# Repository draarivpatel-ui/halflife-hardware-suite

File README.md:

# halflife-hardware-suite

Five hardware design studies built for [Hack Club Half Life](https://halflife.hackclub.com/) and the parametric CAD practice of [Hack Club Atlantis](https://atlantis.hackclub.com/), plus a zero-dependency browser workbench that inspects all five. Everything is checked in as source, fabrication output, firmware, and repeatable tests. No build step, no package manager, no external assets.

Live workbench: <https://aariv.me/halflife-hardware-suite/>

> **PCB fabrication status: not fabrication-ready.** A static audit on 2026-11-25 found incomplete copper connectivity in the week 1, 3, and 4 PCB sources. It also confirmed that weeks 3 and 4 currently emit no board-derived copper tracks in their copper Gerbers because the generator falls back to synthetic pad grids when no exact board capture is passed. Do not upload any PCB Gerber zip until the boards are rerouted, the copper plots are regenerated from real board geometry, and both are independently revalidated.
Repository: <https://github.com/draarivpatel-ui/halflife-hardware-suite>

## Why this exists

Half Life runs five weekly design tracks before five weeks of building: **PCBs**, **CAD**, **music**, **displays**, and **breadboard logic**. Each track qualifies for up to `$100.00` in parts funding, and finishing the program earns a 3D printer and a Half Life sticker sheet. This suite treats each week as a real design exercise with a real BOM, real fabrication files, and a real verification harness rather than a slide deck.

| Week | Track | Project | Board / part count | BOM total |
| --- | --- | --- | --- | --- |
| 1 | PCB | `BenchRail-INA` USB-C dual-rail precision current and voltage monitor | 62 x 42 mm, 2 layer | `$6.90` |
| 2 | CAD | `HelicalDesk` parametric 3-stage snap-fit stand and rotary detent pod | 3 STL + 1 OBJ | print only |
| 3 | Music | `PocketChime-R2R` 8-bit ladder chiptune synthesizer | 78 x 56 mm, 2 layer | `$12.19` |
| 4 | Displays | `GlyphMatrix-128` dual SSD1306 OLED + 74HC595 8x8 LED badge | 88 x 54 mm, 2 layer | `$18.56` |
| 5 | Breadboard logic | `DiscreteALU-74HC` 4-bit CMOS ALU and step counter | 9 DIP ICs | `$12.60` |

All four priced BOMs sit far below the `$100.00` per-project allowance and below the tighter internal caps of `$18.00`, `$22.00`, `$24.00`, and `$16.00`. The combined priced total is `$50.25`, leaving room for shipping, spare passives, and a second prototype round.

## Quick start

```bash
git clone https://github.com/draarivpatel-ui/halflife-hardware-suite.git
cd halflife-hardware-suite
node --test
```

Open `index.html` in any modern browser. It uses plain HTML, CSS, and JavaScript, so it also works from a local file; a static server gives the workbench live access to the checked-in KiCad, STL, and netlist sources. No npm install, no bundler, no CDN.

```bash
python3 -m http.server 8000
# then visit http://localhost:8000/
```

To regenerate every deterministic artifact from one place:

```bash
node tools/generate_suite_artifacts.js
```

The generator uses a seeded PRNG, so re-running it leaves the KiCad boards, Gerbers, drill files, BOMs, STL, OBJ, netlist, and font tables unchanged. The OpenSCAD source remains the authoritative printable geometry for Week 2.

## The five designs

### Week 1: `week1-pcb/` BenchRail-INA

A USB-C powered dual-rail telemetry board. Two `INA219AIDCNR` monitors read independent 0.1 ohm 1% 1206 shunts, one per rail, at I2C addresses 0x40 and 0x41. An `AMS1117-3.3` LDO supplies the logic, a `USB4105-GF-A` receptacle brings in 5 V with 5K1 CC pulldowns, and 0603 decoupling caps sit at every IC. Four M2.5 non-plated mounting holes and a full ground pour complete the layout.

Files: `benchrail_ina.kicad_sch`, `benchrail_ina.kicad_pcb`, `benchrail_ina.kicad_pro`, `gerbers/` (9 RS-274X plots plus Excellon `.drl`), `bom.csv`.

The `.kicad_pro` declares three net classes: Default (0.20 mm clearance / 0.25 mm track), Power (0.25 mm / 0.60 mm), and Signal (0.15 mm / 0.20 mm). Patterns assign VBUS and 3V3 to Power, SDA and SCL to Signal.

**Power-up check:** current-limited 5 V supply, all DIP switches off, idle draw below 30 mA; read the bus voltage register and confirm the calibration word 0x2800 for a 0.1 ohm shunt at a 40 uA LSB.

### Week 2: `week2-cad/` HelicalDesk

`helical_desk.scad` is a fully parameterized OpenSCAD model with Customizer groups for chassis, cradle, dial, snap fit, and assembly. The three printable stages are a base chassis with a raised rim and M2.5 rotary boss, a tilt cradle with side cheeks, rear lip and hinge bore, and a 12-tooth detent dial. No supports are needed; PLA at 0.2 mm layers, 3 perimeters, 15% infill.

`tools/generate_suite_artifacts.js` mirrors the same parameter set and writes `base_chassis.stl`, `tilt_cradle.stl`, `detent_dial.stl`, and `assembled_preview.obj`. `week2-cad/geometry_stats.json` records half-edge pairing, connected components, and signed volume for each part. Every exported STL passes the strict check that each directed edge has exactly one exact opposite, all component volumes are positive, and all stored facet normals agree with their triangle windings.

### Week 3: `week3-music/` PocketChime-R2R

An 8-bit voltage-mode R-2R ladder built from eight 10K horizontal arms and eight 20K vertical legs (seven legs plus a 20K termination), all 0603 1%. An `RP2040-Zero` drives the eight GPIO bits as one bus write; a `MCP6002-I/SN` rail-to-rail dual op amp buffers the ladder into a 3.5 mm TRS jack. Twelve tactile switches form a 3x4 chromatic key matrix.

`firmware/pocketchime.ino` implements four phase-accumulator DDS voices (pulse, triangle, saw, square) and a four-stage ADSR running in a 22050 Hz repeating-timer ISR. The phase increment is `f * 2^32 / sample_rate`; the bus write is a masked GPIO operation.

The workbench solves the ladder by Gaussian elimination on the eight-node Kirchhoff system, giving a strictly monotonic 256-code transfer curve with a uniform 12.891 mV LSB at a 3.3 V reference.

### Week 4: `week4-display/` GlyphMatrix-128

Two 128x64 SSD1306 OLED modules on hardware I2C at 0x3C and 0x3D, plus an 8x8 LED matrix driven by a `74HC595` shift register. `firmware/glyphmatrix.ino` contains a complete SSD1306 init sequence, a 1 KiB page-buffer renderer, a 5x7 bitmap font, and a timer-multiplexed row scan with output blanking during the shift to prevent ghosting.

`font5x7_data.h` carries all 96 printable ASCII glyphs; `font5x7.js` and the root `suite_font.js` carry the full 256-glyph table for the browser simulator. No display library is used.

### Week 5: `week5-logic/` DiscreteALU-74HC

Eight 74HCxx DIP ICs on two 830-point breadboards. A `74HC283` full adder, `74HC86` XOR B-inversion stage, `74HC08` AND, `74HC32` OR, `74HC153` dual 4:1 output mux, `74HC161` step counter, `74HC14` Schmitt debounce, and `74HC02` NOR zero detector. Subtraction uses the two's complement trick: `SUB` drives all four XOR inputs and the adder CIN, so `A + (B XOR SUB) + SUB` equals `A - B`.

`netlist.json` records every physical DIP pin. The 74HC283 pin map was checked against the NXP datasheet Fig 5 (pin configuration), where pin 1 is S2, pin 7 is CIN, pin 9 is COUT, and pin 16 is VCC. `BREADBOARD_GUIDE.md` gives the gate maps, opcode table, flag equations, placement, and a seven-step power-up check. `alu.js` is a gate-level evaluator shared by the Node tests and the browser prover.

## Browser workbench

`index.html` is a six-tab engineering studio:

1. **PCB**: an SVG layer inspector that parses the checked-in `.kicad_pcb` for copper segments, pads, mounting holes, silkscreen text, and Edge.Cuts. Nine independently toggleable layers plus an INA219 register and power model.
2. **CAD**: a Canvas turntable that parses the real ASCII STL, flat-shades it with a depth sort and fixed light vector, supports shaded and wireframe modes, and reports half-edge pairing, signed volume, connected components, and normal agreement.
3. **Music**: the 256-code R-2R staircase alongside an ADSR / four-voice DDS oscilloscope. **No Web Audio object is created on load, on tab switch, or at any point without an explicit user click.** A muted-by-default checkbox creates a silent context; a separate Play control is required before any oscillator starts.
4. **Displays**: two 128x64 page buffers drawn pixel by pixel with a 5x7 font, plus a live 74HC595 8x8 row scan showing the shift register contents.
5. **Logic**: clickable operand bits, five opcodes, gate-level signal flow, flag LEDs, a pin-map browser for all nine ICs, a 74HC161 step counter, and an exhaustive 512 plus 1280 vector verifier.
6. **Lab**: a deterministic Suite Audit & Physics Lab driven by `suite-lab.js`, a pure UMD module with no DOM, network, or timers. It hosts a five-week cross-track comparator (BOM vs cap with headroom and a verified physics metric per week, clickable rows jump into each tab), an R-2R tolerance and INL/DNL sensitivity chart re-solving the real eight-node Kirchhoff system under 46 deterministic worst-case resistor patterns, an INA219 shunt power and ADC full-scale sweep, a clickable BOM-vs-cap budget frontier, and an audited proof brief whose on-page fingerprint, JSON, CSV (formula-injection escaped), and Markdown exports all stamp one cached canonical SHA-256 digest. Lab state round-trips through a fail-closed `#hlab=` URL hash, and an in-page runner executes a 25-check deterministic self-test battery (28 checks once the STL files load) against the live models.

`style.css` is a self-contained dark instrument-panel theme with responsive layouts and reduced-motion support. `.nojekyll` keeps GitHub Pages from ignoring the underscore-prefixed or data files.

## Verification

`node --test` runs 556 tests with thousands of individual assertions:

* KiCad 8 `(version 20240108)` PCB and `(version 20231120)` schematic headers, balanced S-expression parentheses, all nine required layers, net classes, routed copper, pads, courtyards, and four M2.5 holes per board.
* RS-274X `G04`, `%FSLAX46Y46*%`, `%MOMM*%`, aperture definitions, and a terminating `M02*` on all 27 Gerber plots; Excellon `M48`, `FMAT,2`, tool table, `G90`, `G05`, coordinate records, and `M30` on all three drill files.
* BOM CSV structure, real LCSC / DigiKey / JLCPCB part numbers, extended-price arithmetic, and the four price caps.
* STL half-edge manifoldness (every directed edge has its exact opposite), positive signed volume per connected component, and facet normal agreement with triangle winding; OBJ validity for the assembly.
* Exact 256-code R-2R monotonicity with uniform LSB steps, bounded DDS waveforms, and all four ADSR stages.
* SSD1306 1024-byte page-buffer set/get and text rendering, the 256-glyph 5x7 table, and the 74HC595 16-bit scan register model.
* All 512 ADD/SUB operand vectors with exact carry, zero, and overflow, plus all 1280 five-opcode vectors cross-checked between the browser model and `alu.js`.
* Byte-level scan of every file for zero em dashes, zero en dashes, zero AI self-references, backtick-wrapped dollar amounts in Markdown, and no personal contact details.
* The autoplay guard: exactly one `AudioContext` construction site, bound only to a change handler, with gain zero until the separate Play click.
* Lab (`suite-lab.test.js`, discovered beside `test.js`): FIPS 180-4 SHA-256 known-answer vectors plus a 0-to-160-byte boundary sweep against Node `crypto`, canonicalizer key-order, cycle, and depth-bound tests, hostile `#hlab=` codec rejection (`__proto__`, bad roots, bad base64url, clamp violations), R-2R generalized-solver parity with the suite solver across all 256 codes, tolerance-sweep invariants, INA219 sweep bounds, comparator BOM-vs-cap and metric verdicts cross-checked against the real CSVs, formula-injection CSV escaping, single-digest parity across all four export surfaces, one-unit tamper detection, a 160-vector ALU spot grid, the 25-check deterministic self-test battery, and DOM wiring assertions for the sixth tab.

## Repository layout

```
index.html  style.css  suite.js  suite-lab.js  app.js  suite_font.js
test.js  suite-lab.test.js  .nojekyll  README.md  JOURNAL.md  LICENSE
tools/
  generate_suite_artifacts.js   deterministic artifact generator
  font_data.txt                 256 glyph x 5 byte source table
week1-pcb/    kicad_sch  kicad_pcb  kicad_pro  gerbers/  benchrail_ina-gerbers.zip  bom.csv
week2-cad/    helical_desk.scad  3x stl  assembled_preview.obj  geometry_stats.json
week3-music/  kicad_pcb  kicad_pro  gerbers/  pocketchime-gerbers.zip  bom.csv  firmware/pocketchime.ino
week4-display/ kicad_pcb  kicad_pro  gerbers/  glyphmatrix-gerbers.zip  bom.csv  firmware/  font5x7.js
week5-logic/  netlist.json  BREADBOARD_GUIDE.md  alu.js  bom.csv
```

## Fabrication notes

* All PCBs are 2 layer, 1.6 mm FR4, 0.035 mm copper, ENIG finish, green mask, with a 1.51 mm FR4 dielectric core.
* Gerbers use 4.6 format, millimetres, Gerber X2 `%TF.FileFunction` and `%TF.FilePolarity` attributes, and 4.4 metric drill coordinates.
&
* BOM prices are single-unit catalog prices captured for this build. They exclude shipping and customs, which Half Life does not cover.
* Week 2 prints without supports. Allow a 0.2 mm bore clearance on the M2.5 hinge.
* Week 5 uses a current-limited 5 V bench supply and expects under 20 mA idle draw. Tie every unused CMOS input to a defined rail.

## License

MIT. See `LICENSE`.

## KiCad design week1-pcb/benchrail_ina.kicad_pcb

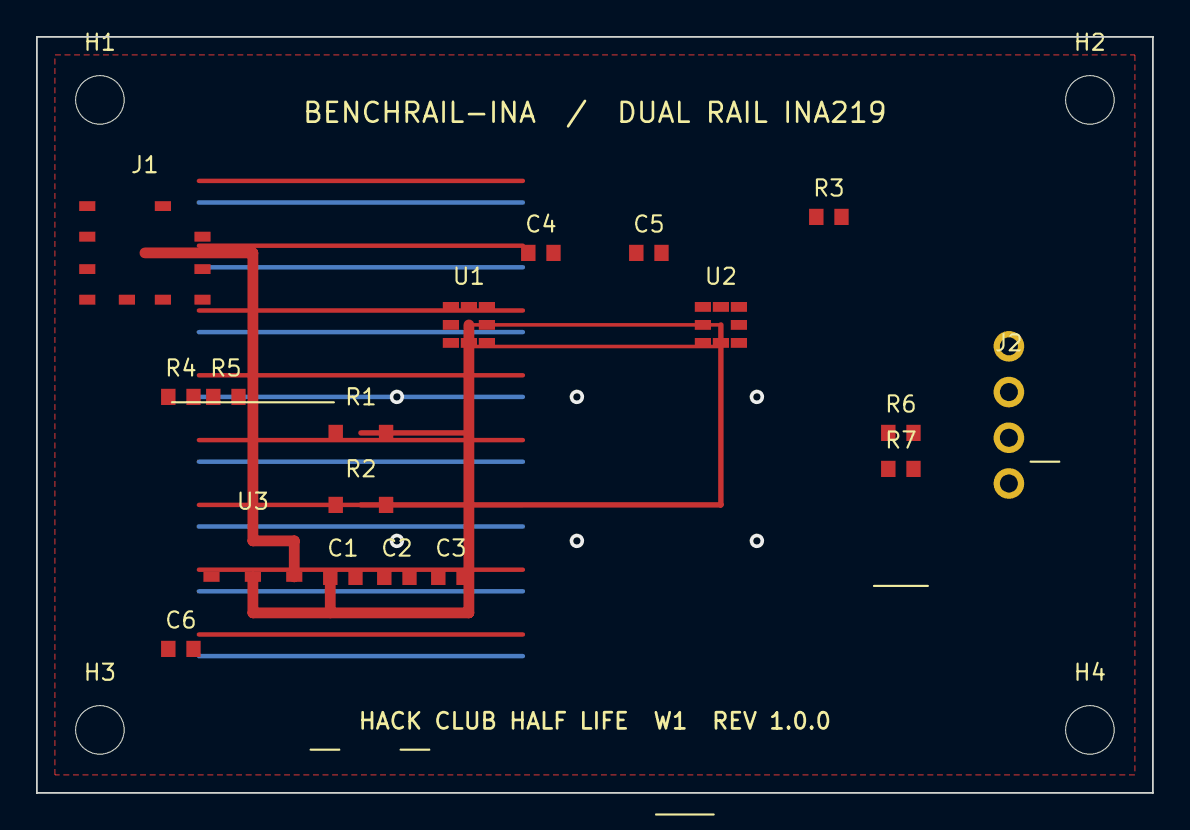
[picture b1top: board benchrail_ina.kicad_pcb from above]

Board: 2 copper layers, 62.0 x 42.0 mm, 22 parts (0 on the bottom side), 14 nets.

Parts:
C1, C4, C5: 100n 0603 X7R; C_0603_1608Metric
C2, C3, C6: 10u 0603 X5R; C_0603_1608Metric
H1, H2, H3, H4: M2.5 nylon screw set; MountingHole_2.7mm_M2.5
J1: USB4105-GF-A; USB_C_Receptacle_GCT_USB4105
J2: 1x04 2.54mm header; PinHeader_1x04_P2.54mm_Vertical
R1, R2: 0R1 1% 1206; R_1206_3216Metric
R3: 10K 1% 0603; R_0603_1608Metric
R4, R5: 5K1 1% 0603; R_0603_1608Metric
R6, R7: 4K7 1% 0603; R_0603_1608Metric
U1, U2: INA219AIDCNR; SOT-23-8
U3: AMS1117-3.3; SOT-223-3_TabPin2

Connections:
+3V3: C1.1, C4.1, C5.1, C6.1, J2.1, R6.2, R7.2, U1.5, U2.5, U3.2
ADDR0: R3.1, U1.6
CC1: J1.A5, R4.1
CC2: J1.B5, R5.1
D+: J1.A6, J1.B6
D-: J1.A7, J1.B7
GND: C1.2, C2.2, C3.2, C4.2, C5.2, C6.2, J1.A1, J1.B1, J2.4, R3.2, R4.2, R5.2, U1.2, U1.8, U2.2, U2.8, U3.1
SCL: J2.3, R7.1, U1.3, U2.3
SDA: J2.2, R6.1, U1.4, U2.4
SHUNT_HI: R1.1, U1.1
SHUNT_LO: R1.2, U1.7
VBUS: C2.1, C3.1, J1.A4, J1.B4, U2.6, U3.3
VRAIL+: R2.1, U2.7
VRAIL-: R2.2, U2.1

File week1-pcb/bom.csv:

Reference,Value,Package,Quantity,Distributor,PartNumber,UnitPriceUSD,ExtendedUSD,Notes
"U1,U2","INA219AIDCNR","SOT-23-8",2,LCSC,C924766,1.38,2.76,"TI INA219, I2C current and voltage monitor"
"U3","AMS1117-3.3","SOT-223-3",1,LCSC,C6186,0.16,0.16,"3.3 V LDO, 1 A"
"J1","USB4105-GF-A","USB-C SMD",1,DigiKey,2073-USB4105-GF-A-ND,0.62,0.62,"GCT USB4105 16 pin USB 2.0 receptacle"
"R1,R2","0R1 1% 1206","1206",2,LCSC,C178685,0.09,0.18,"0.1 ohm 1% 0.25 W sense resistor"
"R3","10K 1% 0603","0603",1,LCSC,C25804,0.01,0.01,"INA219 address select pulldown"
"R4,R5","5K1 1% 0603","0603",2,DigiKey,311-5.10KHRCT-ND,0.02,0.04,"USB-C CC1 and CC2 Rd pulldowns"
"R6,R7","4K7 1% 0603","0603",2,LCSC,C23162,0.01,0.02,"I2C bus pullups to 3V3"
"C1,C4,C5","100n 0603 X7R","0603",3,LCSC,C14663,0.01,0.03,"Decoupling"
"C2,C3,C6","10u 0603 X5R","0603",3,LCSC,C19702,0.03,0.09,"Bulk decoupling"
"J2","1x04 2.54mm header","THT",1,LCSC,C124378,0.11,0.11,"I2C and rail sense breakout"
"H1-H4","M2.5 nylon screw set","Hardware",4,DigiKey,36-9552-ND,0.12,0.48,"M2.5 x 6 mm nylon screws and nuts"
"PCB","BenchRail-INA 2L 62x42mm","FR4",1,JLCPCB,PCB-2L-62x42,2.40,2.40,"2 layer 1.6 mm ENIG, 5 pcs split cost"

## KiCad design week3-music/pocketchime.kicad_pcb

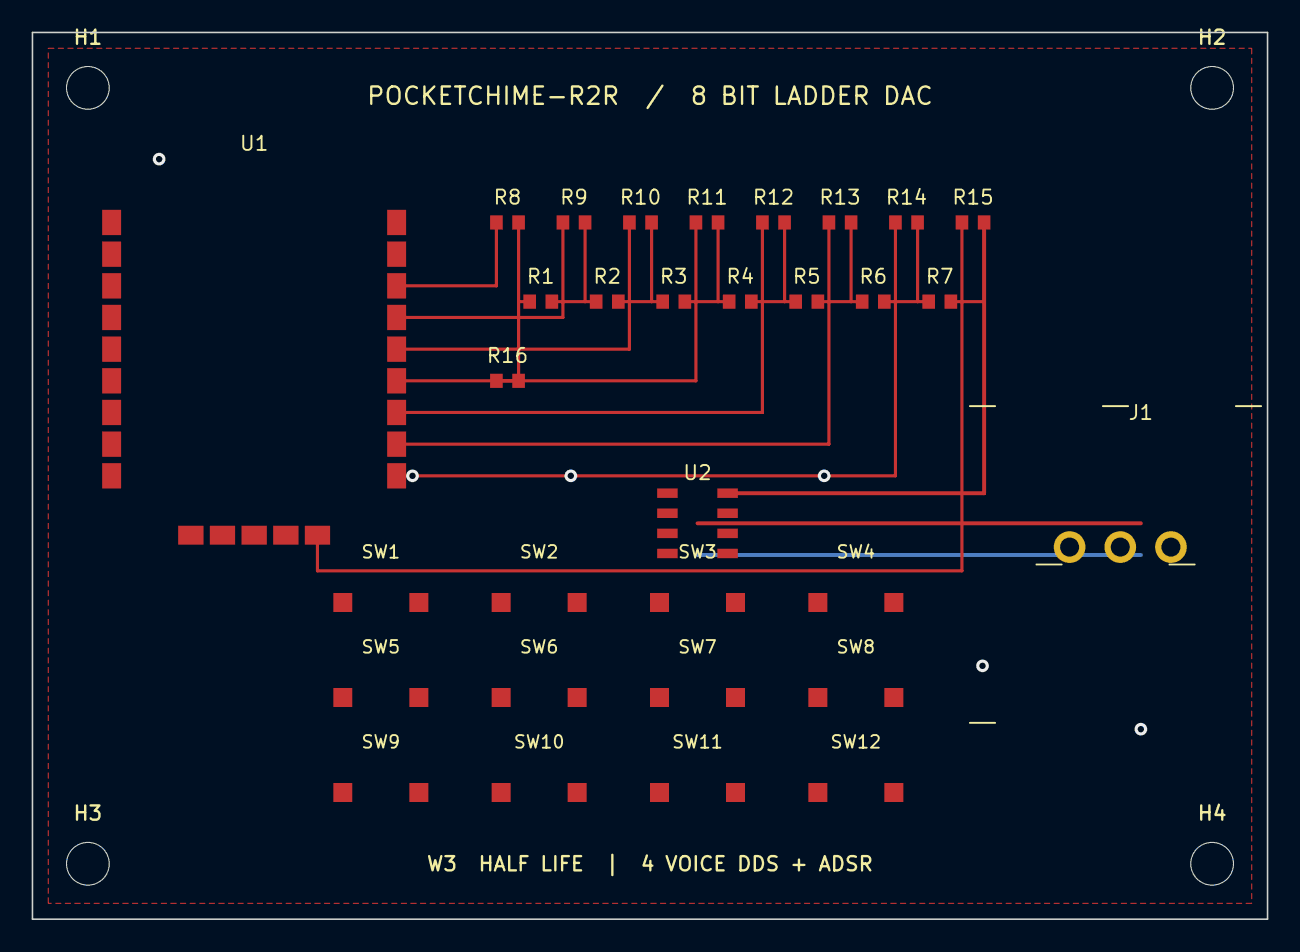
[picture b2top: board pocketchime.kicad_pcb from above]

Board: 2 copper layers, 78.0 x 56.0 mm, 35 parts (0 on the bottom side), 27 nets.

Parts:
H1, H2, H3, H4: MountingHole_2.7mm_M2.5
J1: TRS_3.5mm; Jack_3.5mm_TRS_CUI_SJ1-3523N_Horizontal
R1, R2, R3, R4, R5, R6, R7: 10K 1% 0603; R_0603_1608Metric
R8, R9, R10, R11, R12, R13, R14, R15, R16: 20K 1% 0603; R_0603_1608Metric
SW1, SW2, SW3, SW4, SW5, SW6, SW7, SW8, SW9, SW10, SW11, SW12: TACTILE; SW_SPST_B3U-1000P
U1: RP2040-Zero
U2: MCP6002-I/SN; SOIC-8_3.9x4.9mm_P1.27mm

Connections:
+3V3: U1.3V3, U2.3, U2.8
AUDIO_L: J1.1, U2.1, U2.7
AUDIO_R: J1.2, U2.4
DAC0: R8.1, U1.GP2
DAC1: R9.1, U1.GP3
DAC2: R10.1, U1.GP4
DAC3: R11.1, U1.GP5
DAC4: R12.1, U1.GP6
DAC5: R13.1, U1.GP7
DAC6: R14.1, U1.GP8
DAC7: R15.1, U1.GP9
GND: J1.3, R16.2, U1.GND, U2.2, U2.6
KEY_COL0: SW1.2, SW5.2, SW9.2, U1.GP13
KEY_COL1: SW2.2, SW6.2, SW10.2, U1.GP14
KEY_COL2: SW3.2, SW7.2, SW11.2, U1.GP15
KEY_COL3: SW4.2, SW8.2, SW12.2, U1.GP26
KEY_ROW0: SW1.1, SW2.1, SW3.1, SW4.1, U1.GP10
KEY_ROW1: SW5.1, SW6.1, SW7.1, SW8.1, U1.GP11
KEY_ROW2: SW9.1, SW10.1, SW11.1, SW12.1, U1.GP12
LAD0: R1.1, R8.2, R16.1
LAD1: R1.2, R2.1, R9.2
LAD2: R2.2, R3.1, R10.2
LAD3: R3.2, R4.1, R11.2
LAD4: R4.2, R5.1, R12.2
LAD5: R5.2, R6.1, R13.2
LAD6: R6.2, R7.1, R14.2
LAD7: R7.2, R15.2, U2.5

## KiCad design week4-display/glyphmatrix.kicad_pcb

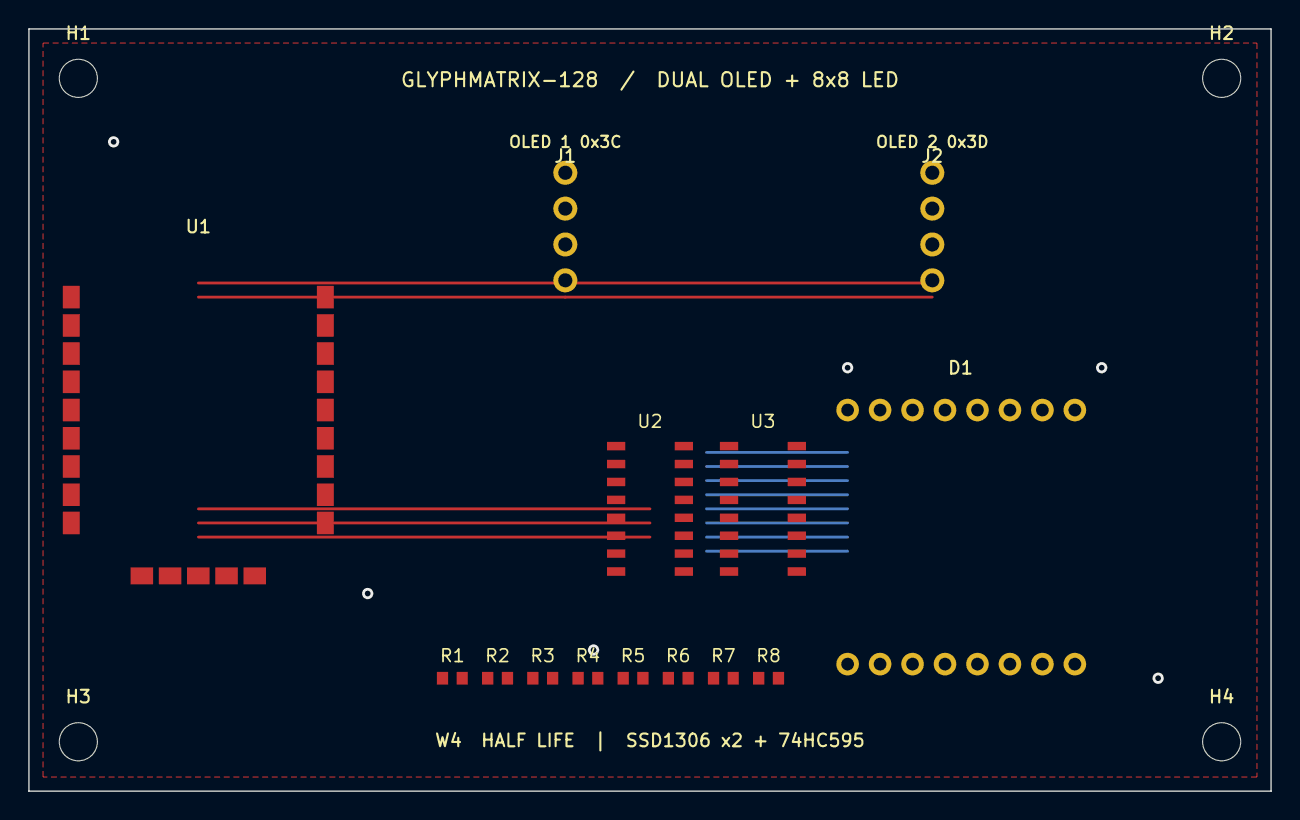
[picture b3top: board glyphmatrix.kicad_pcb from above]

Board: 2 copper layers, 88.0 x 54.0 mm, 18 parts (0 on the bottom side), 25 nets.

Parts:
D1: MATRIX_8x8; LED_Matrix_8x8_20mm
H1, H2, H3, H4: MountingHole_2.7mm_M2.5
J1, J2: SSD1306_128x64; PinHeader_1x04_P2.54mm_Vertical
R1, R2, R3, R4, R5, R6, R7, R8: 330R 0603; R_0603_1608Metric
U1: RP2040-Zero
U2, U3: 74HC595D; SOIC-16_3.9x9.9mm_P1.27mm

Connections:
+3V3: J1.2, J2.2, U1.3V3, U2.10, U2.16, U3.10, U3.16
GND: J1.1, J2.1, R1.2, R2.2, R3.2, R4.2, R5.2, R6.2, R7.2, R8.2, U1.GND, U2.8, U3.8
I2C_SCL: J1.3, J2.3, U1.GP5
I2C_SDA: J1.4, J2.4, U1.GP4
LED_COL0: D1.C0, U2.15
LED_COL1: D1.C1, U2.1
LED_COL2: D1.C2, U2.2
LED_COL3: D1.C3, U2.3
LED_COL4: D1.C4, U2.4
LED_COL5: D1.C5, U2.5
LED_COL6: D1.C6, U2.6
LED_COL7: D1.C7, U2.7
LED_OE: U1.GP9, U2.13, U3.13
LED_ROW0: D1.R0, R1.1, U3.15
LED_ROW1: D1.R1, R2.1, U3.1
LED_ROW2: D1.R2, R3.1, U3.2
LED_ROW3: D1.R3, R4.1, U3.3
LED_ROW4: D1.R4, R5.1, U3.4
LED_ROW5: D1.R5, R6.1, U3.5
LED_ROW6: D1.R6, R7.1, U3.6
LED_ROW7: D1.R7, R8.1, U3.7
SPI_LATCH: U1.GP8, U2.12, U3.12
SPI_MOSI: U1.GP6, U2.14
SPI_SCK: U1.GP7, U2.11, U3.11
SR_CASCADE: U2.9, U3.14
